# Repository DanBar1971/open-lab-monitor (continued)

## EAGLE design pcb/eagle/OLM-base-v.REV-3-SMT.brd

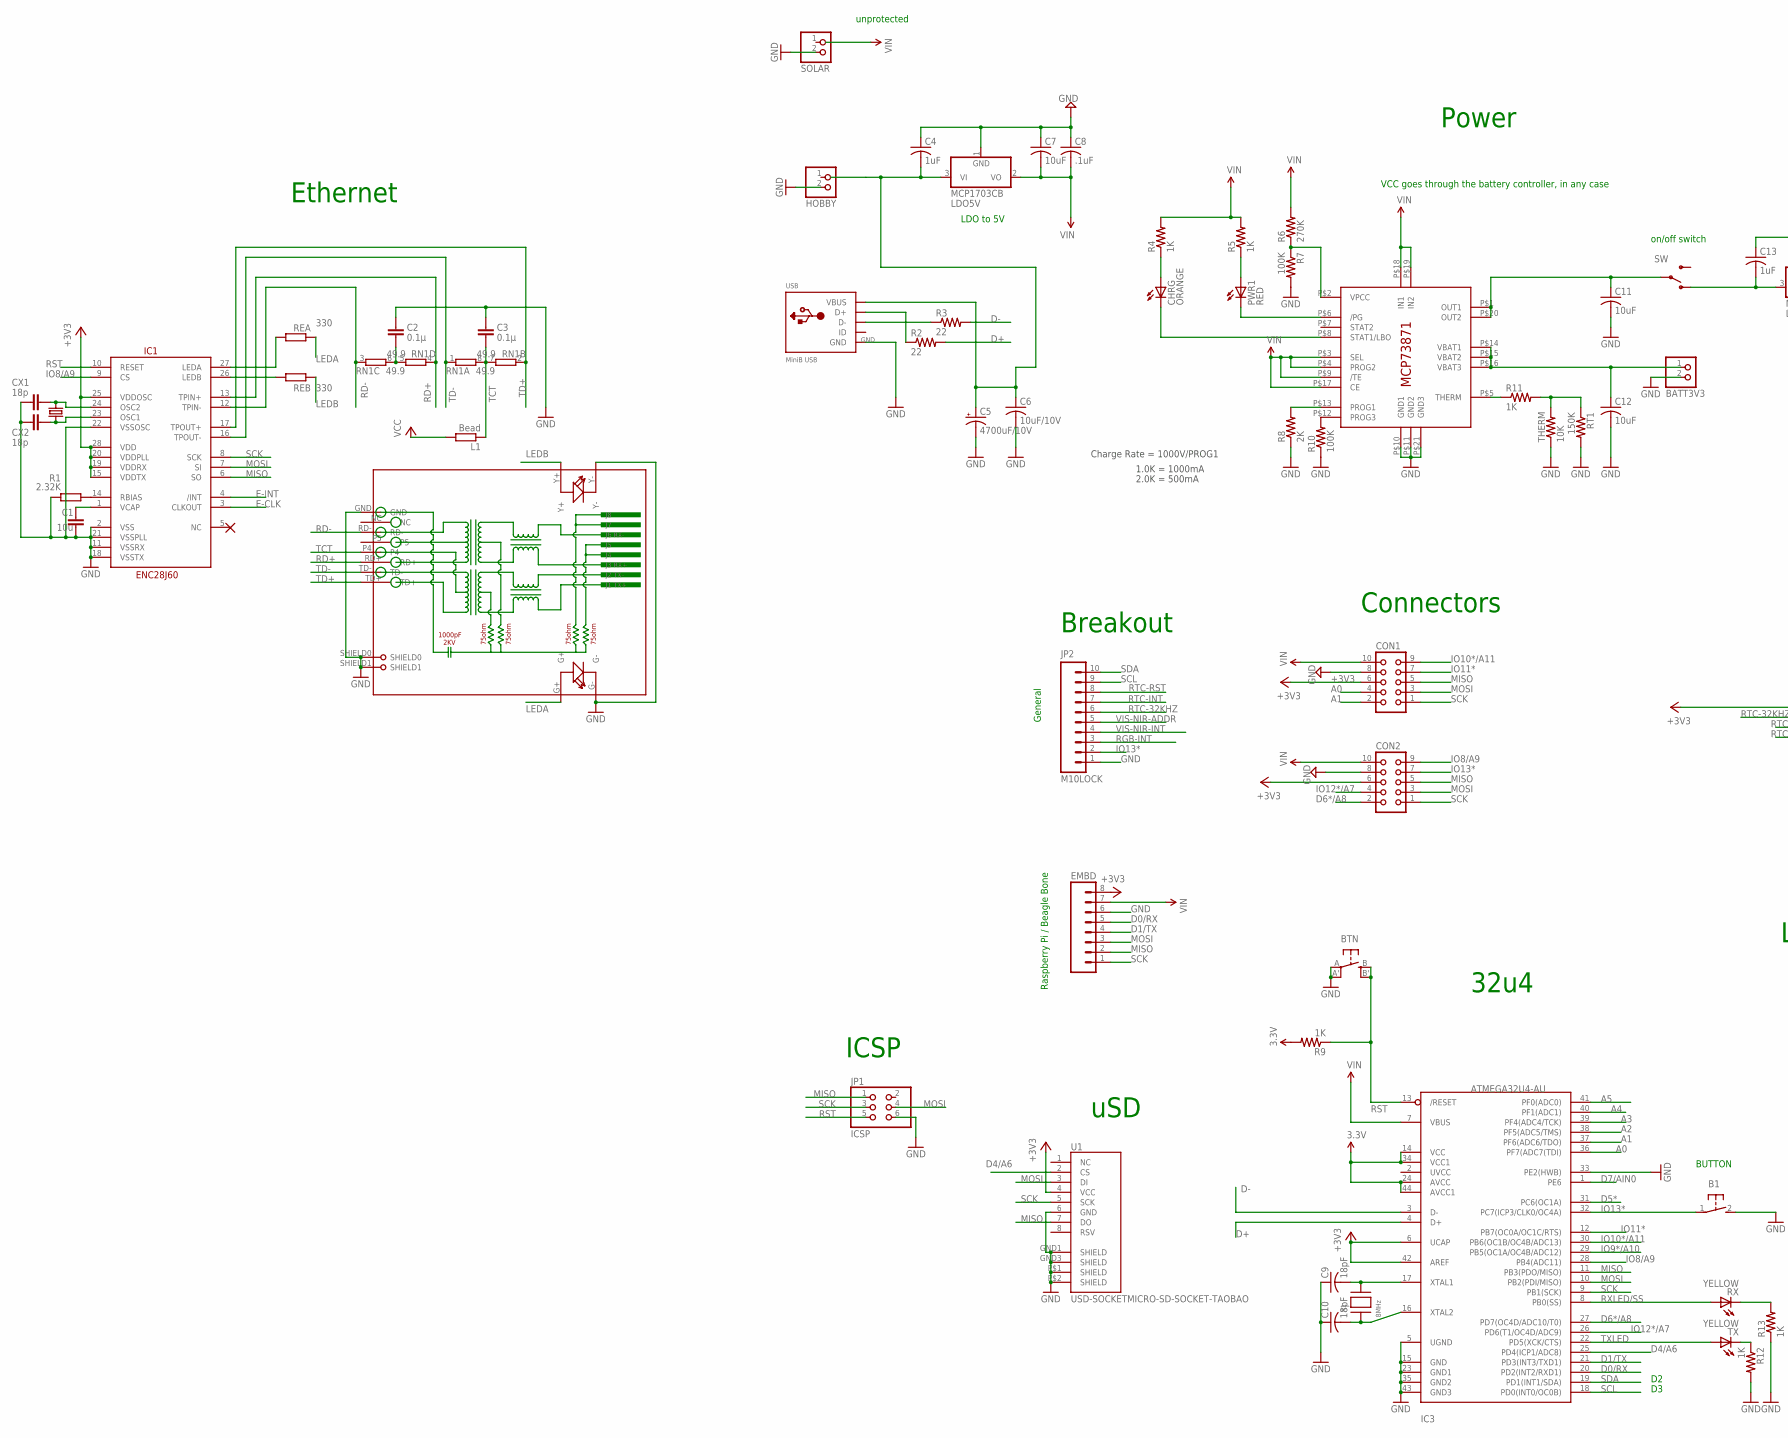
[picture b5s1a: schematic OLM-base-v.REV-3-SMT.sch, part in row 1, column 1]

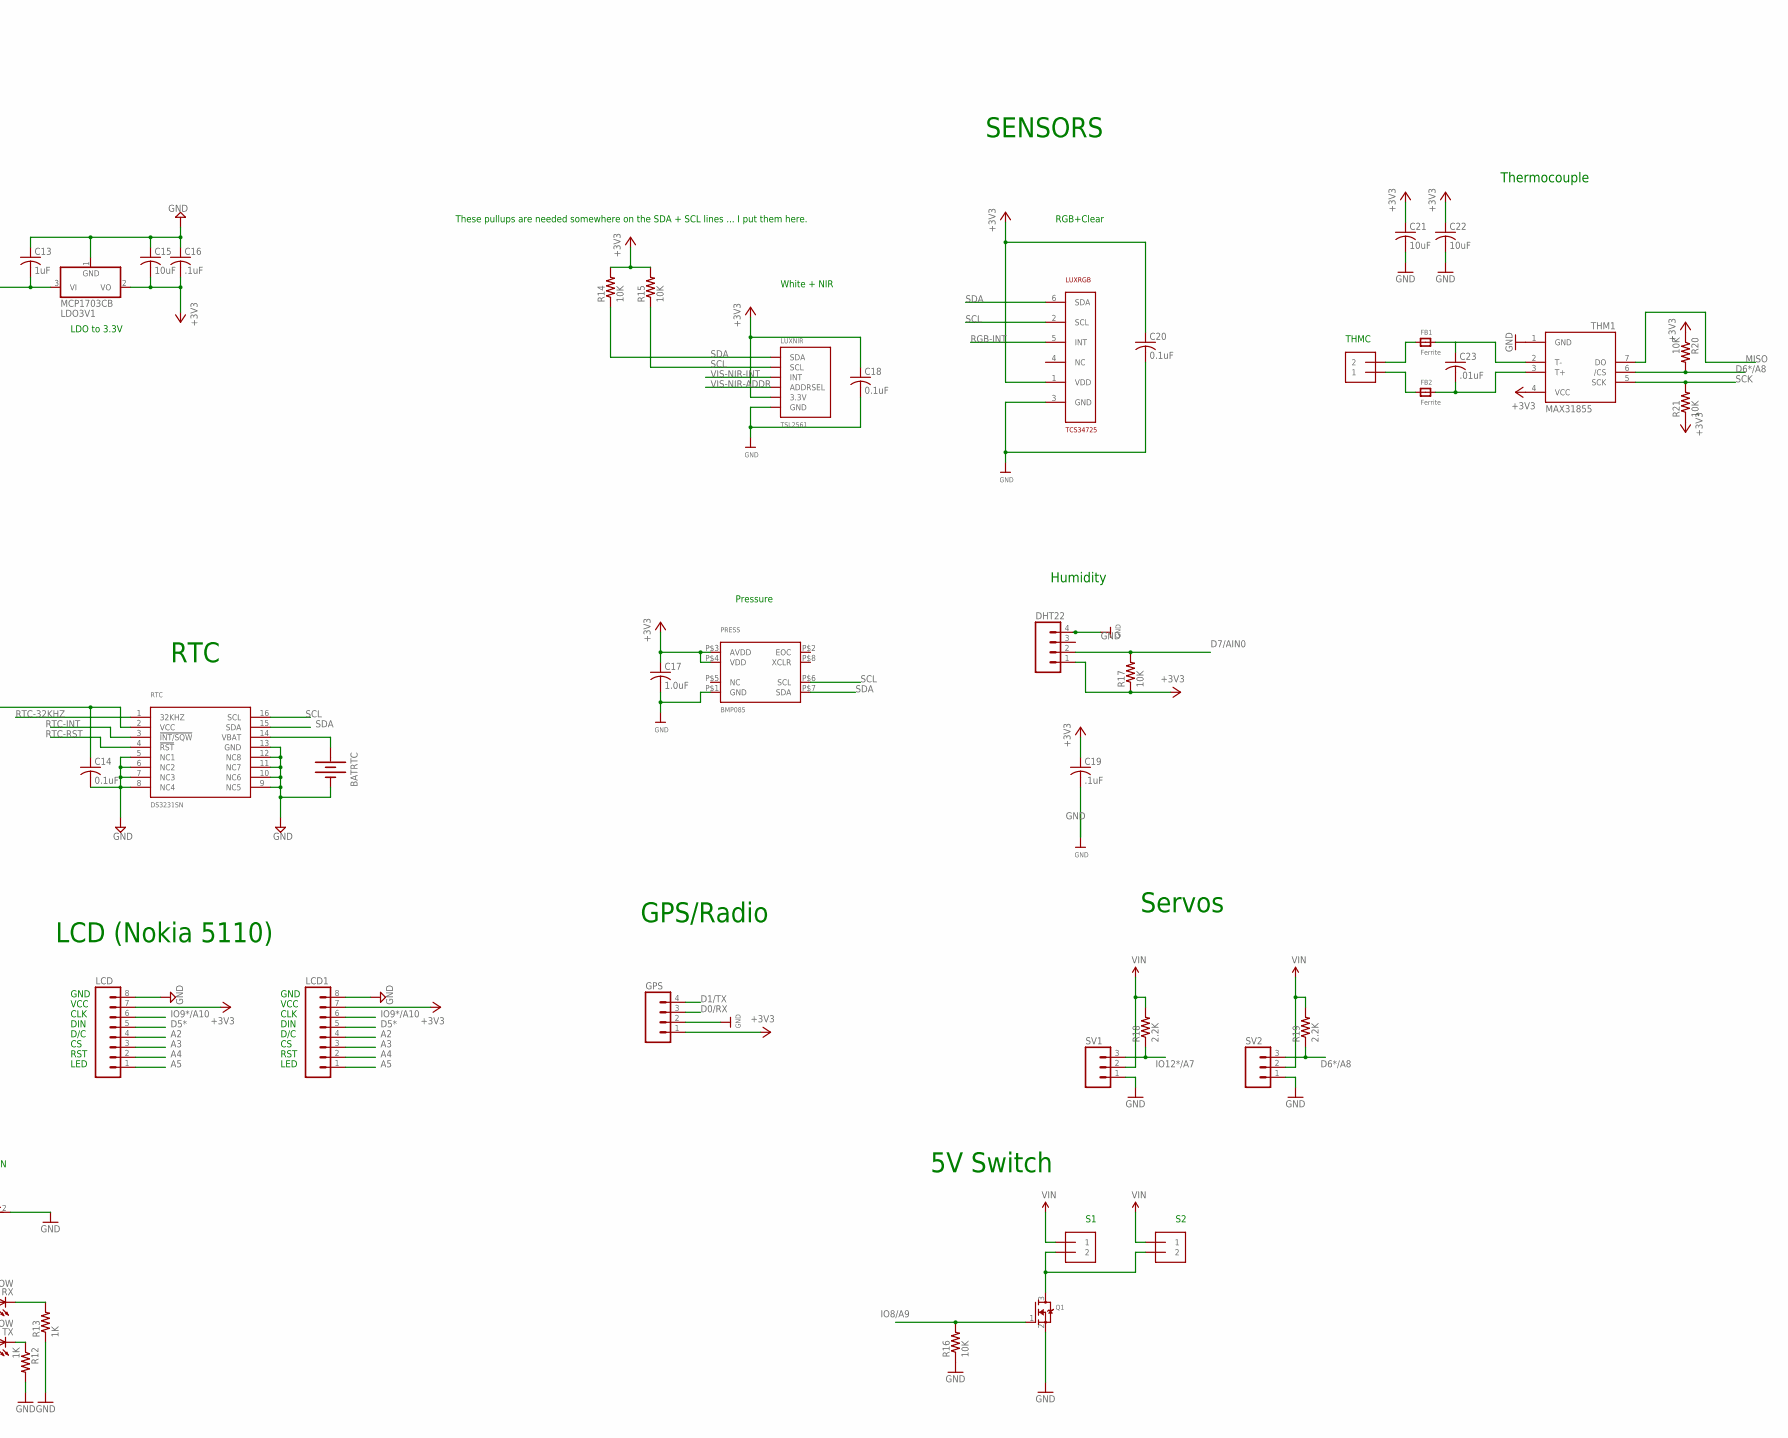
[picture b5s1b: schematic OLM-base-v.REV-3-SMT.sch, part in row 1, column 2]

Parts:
B1: 31-XX; B3F-31XX
BATRTC: BATTERYBATTERY_12MM_SMT; BATTCON_12MM_SMT
BATT3V3: JST_2PIN-SMT-RA; JST-PH-2-SMT-RA
BTN: EVQQ2; EVQ-Q2
C1: 10u; C0805
C2, C3: 0.1µ; C0805
C4, C13: 1uF; C0805
C5: 4700uF/10V; E5-13
C6: 10uF/10V; C0805
C7, C11, C12, C15, C21, C22: 10uF; C0805
C8, C16, C19: .1uF; C0805
C9, C10: 18pF; C0805
C14, C18, C20: 0.1uF; C0805
C17: 1.0uF; C0805
C23: .01uF; C0805
CHRG: ORANGE; CHIP-LED0805
CON1, CON2: CON10L
CX1, CX2: 18p; C0805
DHT22: M04LOCK; 1X04_LOCK
EMBD: M08LOCK; 1X08_LOCK
EXTL: 25MHz; CRYSTAL-SMD-10.5X4.8-2PIN
FB1, FB2: Ferrite; _0805
GPS: M04LOCK; 1X04_LOCK
HOBBY: JST_2PIN-SMT-RA; JST-PH-2-SMT-RA
IC1: ENC28J60; SOIC28WLONG
IC2: MCP73871; QFN20_4MM
IC3: ATMEGA32U4-AU; TQFP44
JP1: ICSP; 2X03
JP2: M10LOCK; 1X10_LOCK
L1: Bead; R0805
LCD, LCD1: M08LOCK; 1X08_LOCK
LDO3V1, LDO5V: MCP1703CB; SOT23
LUXNIR: TSL2561; TSL2561_FN@1
LUXRGB: TCS34725; DFN-6
PRESS: BMP085
PWR1: RED; CHIP-LED0805
Q1: MOSFET-NREFLOW; SOT23
R1: 2.32K; R0805
R2, R3: 22; R0805
R4, R5, R9, R12, R13: 1K; R0805
R6: 270K; R0805
R7, R10: 100K; R0805
R8: 2K; 0805-THM
R11: 1K; M0805
R14, R15, R16, R17, R20, R21: 10K; R0805
R18, R19: 2.2K; R0805
REA: 330; R0805
REB: 330; R0805
RJ1: HR911105A
RN1: 49.9; EXB38V
RT1: 150K; R0805
RTC: DS3231SN; SO16W
RX: YELLOW; CHIPLED_0805
S1, S2: 1X2-3.5MM
SOLAR: JST_2PIN-SMT-RA; JST-PH-2-SMT-RA
SV1, SV2: M03PTH; 1X03
SW: SPDT; SWITCH-SPDT-SMD
THERM: 10K; 0805-THM
THM1: MAX31855; SO08
THMC: 1X2-3.5MM
TX: YELLOW; CHIPLED_0805
U1: USD-SOCKETMICRO-SD-SOCKET-TAOBAO; MICRO-SD-SOCKET-TAOBAO
USB: MiniB USB; USB-MINIB_LARGER
X1: 8MHz; NX5032

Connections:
+3V3: C14.1, C15.2, C16.2, C17.1, C18.1, C19.1, C20.1, C21.1, C22.1, CON1.6, CON2.6, DHT22.1, EMBD.8, GPS.1, IC1.15 (VDDTX), IC1.19 (VDDRX), IC1.20 (VDDPLL), IC1.25 (VDDOSC), IC1.28 (VDD), IC3.6 (UCAP), IC3.42 (AREF), LCD.7, LCD1.7, LDO3V1.2 (VO), LUXNIR.VDD (3.3V), LUXRGB.1 (VDD), PRESS.P$3 (AVDD), PRESS.P$4 (VDD), R14.2, R15.2, R17.1, R20.1, R21.1, RTC.2 (VCC), THM1.4 (VCC), U1.4 (VCC)
A0: CON1.4, IC3.36 (PF7(ADC7(TDI))
A1: CON1.2, IC3.37 (PF6(ADC6/TDO))
A2: IC3.38 (PF5(ADC5/TMS)), LCD.4, LCD1.4
A3: IC3.39 (PF4(ADC4/TCK)), LCD.3, LCD1.3
A4: IC3.40 (PF1(ADC1)), LCD.2, LCD1.2
A5: IC3.41 (PF0(ADC0)), LCD.1, LCD1.1
BATT: BATT3V3.1 (2), C12.1, IC2.P$14 (VBAT1), IC2.P$15 (VBAT2), IC2.P$16 (VBAT3)
D0/RX: EMBD.5, GPS.3, IC3.20 (PD2(INT2/RXD1))
D1/TX: EMBD.4, GPS.4, IC3.21 (PD3(INT3/TXD1))
D4/A6: IC3.25 (PD4(ICP1/ADC8)), U1.2 (CS)
D5*: IC3.31 (PC6(OC1A)), LCD.5, LCD1.5
D6*/A8: CON2.2, IC3.27 (PD7(OC4D/ADC10/T0)), R19.1, R20.2, SV2.3, THM1.6 (/CS)
D7/AIN0: DHT22.2, IC3.1 (PE6), R17.2
D+: IC3.4 (D+), R2.2
D-: IC3.3 (D-), R3.2
E-CLK: IC1.3 (CLKOUT)
E-INT: IC1.4 (/INT)
GND: B1.2 (S), BATRTC.P$1 (-), BATT3V3.2 (1), BTN.A, BTN.A' (P1), C1.2, C2.1, C3.1, C4.1, C5.-, C6.2, C7.1, C8.1, C9.1, C10.1, C11.2, C12.2, C13.1, C14.2, C15.1, C16.1, C17.2, C18.2, C19.2, C20.2, C21.2, C22.2, CON1.8, CON2.8, CX1.2, CX2.2, DHT22.4, EMBD.6, GPS.2, HOBBY.2 (1), IC1.2 (VSS), IC1.11 (VSSRX), IC1.18 (VSSTX), IC1.21 (VSSPLL), IC1.22 (VSSOSC), IC2.P$10 (GND1), IC2.P$11 (GND2), IC2.P$21 (GND3), IC3.5 (UGND), IC3.15 (GND), IC3.23 (GND1), IC3.33 (PE2(HWB)), IC3.35 (GND2), IC3.43 (GND3), JP1.6, JP2.1, LCD.8, LCD1.8, LDO3V1.1 (GND), LDO5V.1 (GND), LUXNIR.VSS (GND), LUXRGB.3 (GND), PRESS.P$1 (GND), Q1.2 (S), R1.1, R7.2, R8.1, R10.1, R12.2, R13.1, R16.1, RJ1.G-, RJ1.GND, RJ1.SHIELD0, RJ1.SHIELD1, RJ1.Y-, RT1.2, RTC.5 (NC1), RTC.6 (NC2), RTC.7 (NC3), RTC.8 (NC4), RTC.9 (NC5), RTC.10 (NC6), RTC.11 (NC7), RTC.12 (NC8), RTC.13 (GND), SOLAR.2 (1), SV1.1, SV2.1, THERM.1, THM1.1 (GND), U1.6 (GND), U1.GND1 (SHIELD), U1.GND3 (SHIELD), U1.P$1 (SHIELD), U1.P$2 (SHIELD), USB.GND
HIGH-CURRENT: Q1.3 (D), S1.2, S2.2
IO8/A9: CON2.9, IC1.9 (CS), IC3.28 (PB4(ADC11)), Q1.1 (G), R16.2
IO9*/A10: IC3.29 (PB5(OC1A/OC4B/ADC12)), LCD.6, LCD1.6
IO10*/A11: CON1.9, IC3.30 (PB6(OC1B/OC4B/ADC13))
IO11*: CON1.7, IC3.12 (PB7(OC0A/OC1C/RTS))
IO12*/A7: CON2.4, IC3.26 (PD6(T1/OC4D/ADC9)), R18.1, SV1.3
IO13*: B1.1, CON2.7, IC3.32 (PC7(ICP3/CLK0/OC4A))
LEDA: REA.2, RJ1.G+
LEDB: REB.2, RJ1.Y+
MISO: CON1.5, CON2.5, EMBD.2, IC1.6 (SO), IC3.11 (PB3(PDO/MISO)), JP1.1, THM1.7 (DO), U1.7 (DO)
MOSI: CON1.3, CON2.3, EMBD.3, IC1.7 (SI), IC3.10 (PB2(PDI/MISO)), JP1.4, U1.3 (DI)
unnamed: BATRTC.P$2 (+), RTC.14 (VBAT)
unnamed: IC1.27 (LEDA), REA.1
unnamed: FB1.1, THMC.2
unnamed: C23.1, FB1.2, THM1.2 (T-)
unnamed: FB2.1, THMC.1
unnamed: C23.2, FB2.2, THM1.3 (T+)
unnamed: C9.2, IC3.17 (XTAL1), X1.P$2
unnamed: C10.2, IC3.16 (XTAL2), X1.P$1
unnamed: C2.2, RN1.5 (2), RN1.6 (2)
unnamed: R12.1, TX.C
unnamed: R13.2, RX.C
unnamed: IC1.26 (LEDB), REB.1
unnamed: C1.1, IC1.1 (VCAP)
unnamed: IC1.14 (RBIAS), R1.2
unnamed: CX1.1, EXTL.P$2 (2), IC1.24 (OSC2)
unnamed: CX2.1, EXTL.P$1 (1), IC1.23 (OSC1)
unnamed: IC2.P$2 (VPCC), R6.1, R7.1
unnamed: IC2.P$6 (/PG), PWR1.C
unnamed: C4.2, C5.+, C6.1, LDO5V.3 (VI), USB.VBUS
unnamed: CHRG.C, IC2.P$8 (STAT1/LBO)
unnamed: CHRG.A, R4.1
unnamed: PWR1.A, R5.1
unnamed: IC2.P$12 (PROG3), R10.2
unnamed: IC2.P$13 (PROG1), R8.2
unnamed: C11.1, IC2.P$1 (OUT1), IC2.P$20 (OUT2), SW.2
unnamed: IC2.P$5 (THERM), R11.1
unnamed: R11.2, RT1.1, THERM.2
unnamed: R2.1, USB.D+
unnamed: R3.1, USB.D-
unnamed: C13.2, LDO3V1.3 (VI)
RD+: IC1.13 (TPIN+), RJ1.RD+, RN1.4 (1)
RD-: IC1.12 (TPIN-), RJ1.RD-, RN1.3 (1)
RGB-INT: LUXRGB.5 (INT)
RST: BTN.B (S), BTN.B' (S1), IC1.10 (RESET), IC3.13 (/RESET), JP1.5, R9.1
RTC-32KHZ: RTC.1 (32KHZ)
RTC-INT: RTC.3 (!INT/SQW)
RTC-RST: RTC.4 (!RST)
RXLED/SS: IC3.8 (PB0(SS)), RX.A
SCK: CON1.1, CON2.1, EMBD.1, IC1.8 (SCK), IC3.9 (PB1(SCK)), JP1.3, R21.2, THM1.5 (SCK), U1.5 (SCK)
SCL: IC3.18 (PD0(INT0/OC0B)), JP2.9, LUXNIR.CLK (SCL), LUXRGB.2 (SCL), PRESS.P$6 (SCL), R15.1, RTC.16 (SCL)
SDA: IC3.19 (PD1(INT1/SDA)), JP2.10, LUXNIR.DATA (SDA), LUXRGB.6 (SDA), PRESS.P$7 (SDA), R14.1, RTC.15 (SDA)
TCT: C3.2, L1.1, RJ1.P4, RN1.7 (2), RN1.8 (2)
TD+: IC1.17 (TPOUT+), RJ1.TD+, RN1.2 (1)
TD-: IC1.16 (TPOUT-), RJ1.TD-, RN1.1
TXLED: IC3.22 (PD5(XCK/CTS)), TX.A
VCC: IC3.14 (VCC), IC3.24 (AVCC), IC3.34 (VCC1), IC3.44 (AVCC1), L1.2, R9.2
VIN: C7.2, C8.2, CON1.10, CON2.10, EMBD.7, IC2.P$3 (SEL), IC2.P$4 (PROG2), IC2.P$9 (/TE), IC2.P$17 (CE), IC2.P$18 (IN1), IC2.P$19 (IN2), IC3.7 (VBUS), LDO5V.2 (VO), R4.2, R5.2, R6.2, R18.2, R19.2, S1.1, S2.1, SV1.2, SV2.2
VIS-NIR-ADDR: LUXNIR.ADR (ADDRSEL)
VIS-NIR-INT: LUXNIR.INT

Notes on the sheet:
Power
uSD
32u4
Connectors
ICSP
Ethernet
Breakout
RTC
RGB+Clear
White + NIR
Pressure
Charge Rate = 1000V/PROG1
1.0K = 1000mA
2.0K = 500mA
Humidity
on/off switch
VCC goes through the battery controller, in any case
SENSORS
These pullups are needed somewhere on the SDA + SCL lines ... I put them here.
LED
RST
D/C
DIN
CLK
VCC
GND
Thermocouple
LDO to 5V
LDO to 3.3V
General
Raspberry Pi / Beagle Bone
unprotected
BUTTON
LCD (Nokia 5110)
GPS/Radio
Servos
5V Switch
THMC

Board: 2 copper layers, 95 parts (0 on the bottom side), 71 nets, no tracks yet.

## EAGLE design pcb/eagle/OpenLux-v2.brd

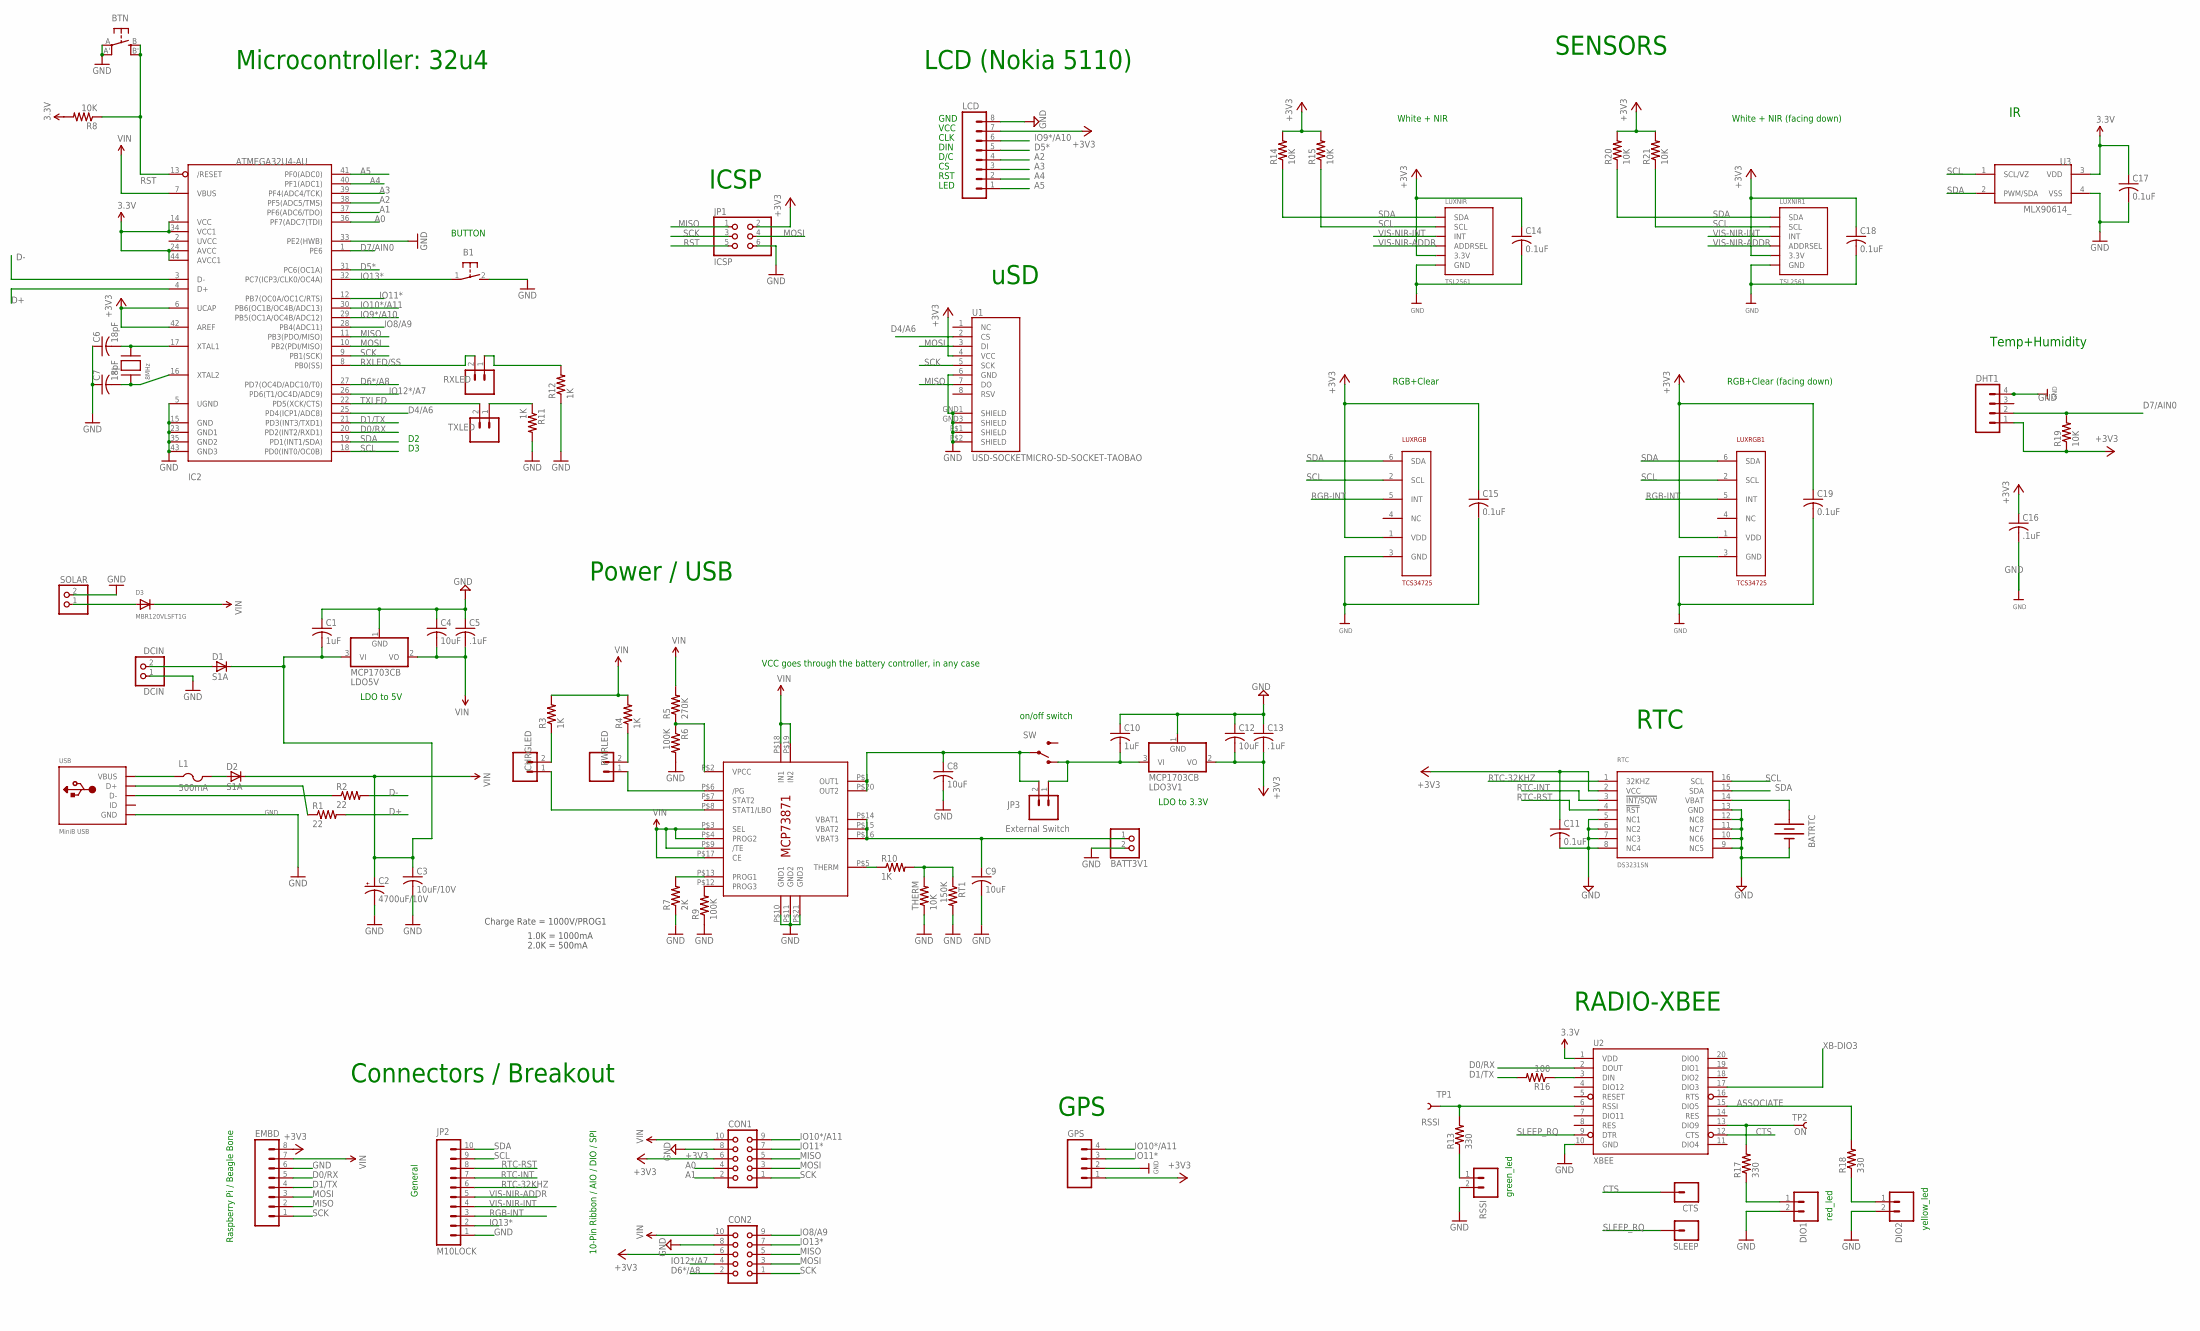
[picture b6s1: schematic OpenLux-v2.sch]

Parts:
B1: 31-XX; B3F-31XX
BATRTC: BATTERYBATTERY_12MM_SMT; BATTCON_12MM_SMT
BATT3V1: JST_2PIN-SMT-RA; JST-PH-2-SMT-RA
BTN: EVQQ2; EVQ-Q2
C1, C10: 1uF; C0805
C2: 4700uF/10V; E5-13
C3: 10uF/10V; C0805
C4, C8, C9, C12: 10uF; C0805
C5, C13, C16: .1uF; C0805
C6, C7: 18pF; C0805
C11, C14, C15, C17, C18, C19: 0.1uF; C0805
CHRGLED: M02PTH; 1X02
CON1, CON2: CON10L
CTS: M01PTH; 1X01
D1, D2: S1A; DO-214AC
D3: MBR120VLSFT1G; SOD-123
DCIN: DCIN; 1X02_OVAL
DHT1: M04LOCK; 1X04_LOCK
DIO1, DIO2: M02PTH; 1X02
EMBD: M08LOCK; 1X08_LOCK
GPS: M04LOCK; 1X04_LOCK
IC1: MCP73871; QFN20_4MM
IC2: ATMEGA32U4-AU; TQFP44
JP1: ICSP; 2X03
JP2: M10LOCK; 1X10_LOCK
JP3: External Switch; 1X02
L1: 500mA; R1206
LCD: M08LOCK; 1X08_LOCK
LDO3V1, LDO5V: MCP1703CB; SOT23
LUXNIR, LUXNIR1: TSL2561; TSL2561_FN@1
LUXRGB, LUXRGB1: TCS34725; DFN-6
PWRLED: M02PTH; 1X02
R1, R2: 22; R0805
R3, R4, R11, R12: 1K; R0805
R5: 270K; R0805
R6, R9: 100K; R0805
R7: 2K; 0805-THM
R8, R14, R15, R19, R20, R21: 10K; R0805
R10: 1K; M0805
R13, R17, R18: 330; R0805
R16: 100; R0805
RSSI: M02PTH; 1X02
RT1: 150K; R0805
RTC: DS3231SN; SO16W
RXLED: M02PTH; 1X02
SLEEP: M01PTH; 1X01
SOLAR: JST_2PIN-SMT-RA; JST-PH-2-SMT-RA
SW: SPDT; SWITCH-SPDT-SMD
THERM: 10K; 0805-THM
TP1: RSSI; PAD.03X.05
TP2: ON; PAD.03X.05
TXLED: M02PTH; 1X02
U1: USD-SOCKETMICRO-SD-SOCKET-TAOBAO; MICRO-SD-SOCKET-TAOBAO
U2: XBEE; XBEE-SMD
U3: MLX90614_; TO-39
USB: MiniB USB; USB-MINIB_LARGER
X1: 8MHz; NX5032

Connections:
3.3V: C17.1, U2.1 (VDD), U3.3 (VDD)
+3V3: C11.1, C12.2, C13.2, C14.1, C15.1, C16.1, C18.1, C19.1, CON1.6, CON2.6, DHT1.1, EMBD.8, GPS.1, IC2.6 (UCAP), IC2.42 (AREF), JP1.2, LCD.7, LDO3V1.2 (VO), LUXNIR.VDD (3.3V), LUXNIR1.VDD (3.3V), LUXRGB.1 (VDD), LUXRGB1.1 (VDD), R14.2, R15.2, R19.1, R20.2, R21.2, RTC.2 (VCC), U1.4 (VCC)
A0: CON1.4, IC2.36 (PF7(ADC7(TDI))
A1: CON1.2, IC2.37 (PF6(ADC6/TDO))
A2: IC2.38 (PF5(ADC5/TMS)), LCD.4
A3: IC2.39 (PF4(ADC4/TCK)), LCD.3
A4: IC2.40 (PF1(ADC1)), LCD.2
A5: IC2.41 (PF0(ADC0)), LCD.1
ASSOCIATE: R18.2, U2.15 (DIO5)
BATT: BATT3V1.1 (2), C9.1, IC1.P$14 (VBAT1), IC1.P$15 (VBAT2), IC1.P$16 (VBAT3)
CTS: CTS.1, U2.12 (CTS)
D0/RX: EMBD.5, IC2.20 (PD2(INT2/RXD1)), U2.2 (DOUT)
D1/TX: EMBD.4, IC2.21 (PD3(INT3/TXD1)), R16.2
D4/A6: IC2.25 (PD4(ICP1/ADC8)), U1.2 (CS)
D5*: IC2.31 (PC6(OC1A)), LCD.5
D6*/A8: CON2.2, IC2.27 (PD7(OC4D/ADC10/T0))
D7/AIN0: DHT1.2, IC2.1 (PE6), R19.2
D+: IC2.4 (D+), R1.2
D-: IC2.3 (D-), R2.2
GND: B1.2 (S), BATRTC.P$1 (-), BATT3V1.2 (1), BTN.A, BTN.A' (P1), C1.1, C2.-, C3.2, C4.1, C5.1, C6.1, C7.1, C8.2, C9.2, C10.1, C11.2, C12.1, C13.1, C14.2, C15.2, C16.2, C17.2, C18.2, C19.2, CON1.8, CON2.8, DCIN.1, DHT1.4, DIO1.2, DIO2.2, EMBD.6, GPS.2, IC1.P$10 (GND1), IC1.P$11 (GND2), IC1.P$21 (GND3), IC2.5 (UGND), IC2.15 (GND), IC2.23 (GND1), IC2.33 (PE2(HWB)), IC2.35 (GND2), IC2.43 (GND3), JP1.6, JP2.1, LCD.8, LDO3V1.1 (GND), LDO5V.1 (GND), LUXNIR.VSS (GND), LUXNIR1.VSS (GND), LUXRGB.3 (GND), LUXRGB1.3 (GND), R6.2, R7.1, R9.1, R11.2, R12.1, RSSI.2, RT1.2, RTC.5 (NC1), RTC.6 (NC2), RTC.7 (NC3), RTC.8 (NC4), RTC.9 (NC5), RTC.10 (NC6), RTC.11 (NC7), RTC.12 (NC8), RTC.13 (GND), SOLAR.2 (1), THERM.1, U1.6 (GND), U1.GND1 (SHIELD), U1.GND3 (SHIELD), U1.P$1 (SHIELD), U1.P$2 (SHIELD), U2.10 (GND), U3.4 (VSS), USB.GND
IO8/A9: CON2.9, IC2.28 (PB4(ADC11))
IO9*/A10: IC2.29 (PB5(OC1A/OC4B/ADC12)), LCD.6
IO10*/A11: CON1.9, GPS.4, IC2.30 (PB6(OC1B/OC4B/ADC13))
IO11*: CON1.7, GPS.3, IC2.12 (PB7(OC0A/OC1C/RTS))
IO12*/A7: CON2.4, IC2.26 (PD6(T1/OC4D/ADC9))
IO13*: B1.1, CON2.7, IC2.32 (PC7(ICP3/CLK0/OC4A)), JP2.2
MISO: CON1.5, CON2.5, EMBD.2, IC2.11 (PB3(PDO/MISO)), JP1.1, U1.7 (DO)
MOSI: CON1.3, CON2.3, EMBD.3, IC2.10 (PB2(PDI/MISO)), JP1.4, U1.3 (DI)
unnamed: BATRTC.P$2 (+), RTC.14 (VBAT)
unnamed: R17.2, TP2.P$1, U2.13 (DIO9)
unnamed: R13.1, RSSI.1
unnamed: R13.2, TP1.P$1, U2.6 (RSSI)
unnamed: R16.1, U2.3 (DIN)
unnamed: DIO1.1, R17.1
unnamed: D1.A, DCIN.2
unnamed: C6.2, IC2.17 (XTAL1), X1.P$2
unnamed: C7.2, IC2.16 (XTAL2), X1.P$1
unnamed: R11.1, TXLED.1
unnamed: R12.2, RXLED.1
unnamed: L1.1, USB.VBUS
unnamed: DIO2.1, R18.1
unnamed: IC1.P$2 (VPCC), R5.1, R6.1
unnamed: IC1.P$6 (/PG), PWRLED.1
unnamed: D3.A, SOLAR.1 (2)
unnamed: D2.A, L1.2
unnamed: CHRGLED.1, IC1.P$8 (STAT1/LBO)
unnamed: CHRGLED.2, R3.1
unnamed: PWRLED.2, R4.1
unnamed: IC1.P$12 (PROG3), R9.2
unnamed: IC1.P$13 (PROG1), R7.2
unnamed: C8.1, IC1.P$1 (OUT1), IC1.P$20 (OUT2), JP3.2, SW.2
unnamed: IC1.P$5 (THERM), R10.1
unnamed: R10.2, RT1.1, THERM.2
unnamed: R1.1, USB.D+
unnamed: R2.1, USB.D-
unnamed: C10.2, JP3.1, LDO3V1.3 (VI), SW.1 (O)
RGB-INT: JP2.3, LUXRGB.5 (INT), LUXRGB1.5 (INT)
RST: BTN.B (S), BTN.B' (S1), IC2.13 (/RESET), JP1.5, R8.1
RTC-32KHZ: JP2.6, RTC.1 (32KHZ)
RTC-INT: JP2.7, RTC.3 (!INT/SQW)
RTC-RST: JP2.8, RTC.4 (!RST)
RXLED/SS: IC2.8 (PB0(SS)), RXLED.2
SCK: CON1.1, CON2.1, EMBD.1, IC2.9 (PB1(SCK)), JP1.3, U1.5 (SCK)
SCL: IC2.18 (PD0(INT0/OC0B)), JP2.9, LUXNIR.CLK (SCL), LUXNIR1.CLK (SCL), LUXRGB.2 (SCL), LUXRGB1.2 (SCL), R15.1, R21.1, RTC.16 (SCL), U3.1 (SCL/VZ)
SDA: IC2.19 (PD1(INT1/SDA)), JP2.10, LUXNIR.DATA (SDA), LUXNIR1.DATA (SDA), LUXRGB.6 (SDA), LUXRGB1.6 (SDA), R14.1, R20.1, RTC.15 (SDA), U3.2 (PWM/SDA)
SLEEP_RQ: SLEEP.1, U2.9 (DTR)
TXLED: IC2.22 (PD5(XCK/CTS)), TXLED.2
VCC: IC2.14 (VCC), IC2.24 (AVCC), IC2.34 (VCC1), IC2.44 (AVCC1), R8.2
VIN: C1.2, C2.+, C3.1, C4.2, C5.2, CON1.10, CON2.10, D1.C, D2.C, D3.C, EMBD.7, IC1.P$3 (SEL), IC1.P$4 (PROG2), IC1.P$9 (/TE), IC1.P$17 (CE), IC1.P$18 (IN1), IC1.P$19 (IN2), IC2.7 (VBUS), LDO5V.2 (VO), LDO5V.3 (VI), R3.2, R4.2, R5.2
VIS-NIR-ADDR: JP2.5, LUXNIR.ADR (ADDRSEL), LUXNIR1.ADR (ADDRSEL)
VIS-NIR-INT: JP2.4, LUXNIR.INT, LUXNIR1.INT
XB-DIO3: U2.17 (DIO3)

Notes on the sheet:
Power / USB
uSD
Microcontroller: 32u4
Connectors / Breakout
ICSP
RTC
RGB+Clear
White + NIR
Charge Rate = 1000V/PROG1
1.0K = 1000mA
2.0K = 500mA
Temp+Humidity
on/off switch
VCC goes through the battery controller, in any case
SENSORS
LED
RST
D/C
DIN
CLK
VCC
GND
LDO to 5V
LDO to 3.3V
General
Raspberry Pi / Beagle Bone
BUTTON
LCD (Nokia 5110)
GPS
red_led
yellow_led
green_led
RADIO-XBEE
10-Pin Ribbon / AIO / DIO / SPI
RGB+Clear (facing down)
White + NIR (facing down)

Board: 2 copper layers, 87 parts (3 on the bottom side), 71 nets, no tracks yet.

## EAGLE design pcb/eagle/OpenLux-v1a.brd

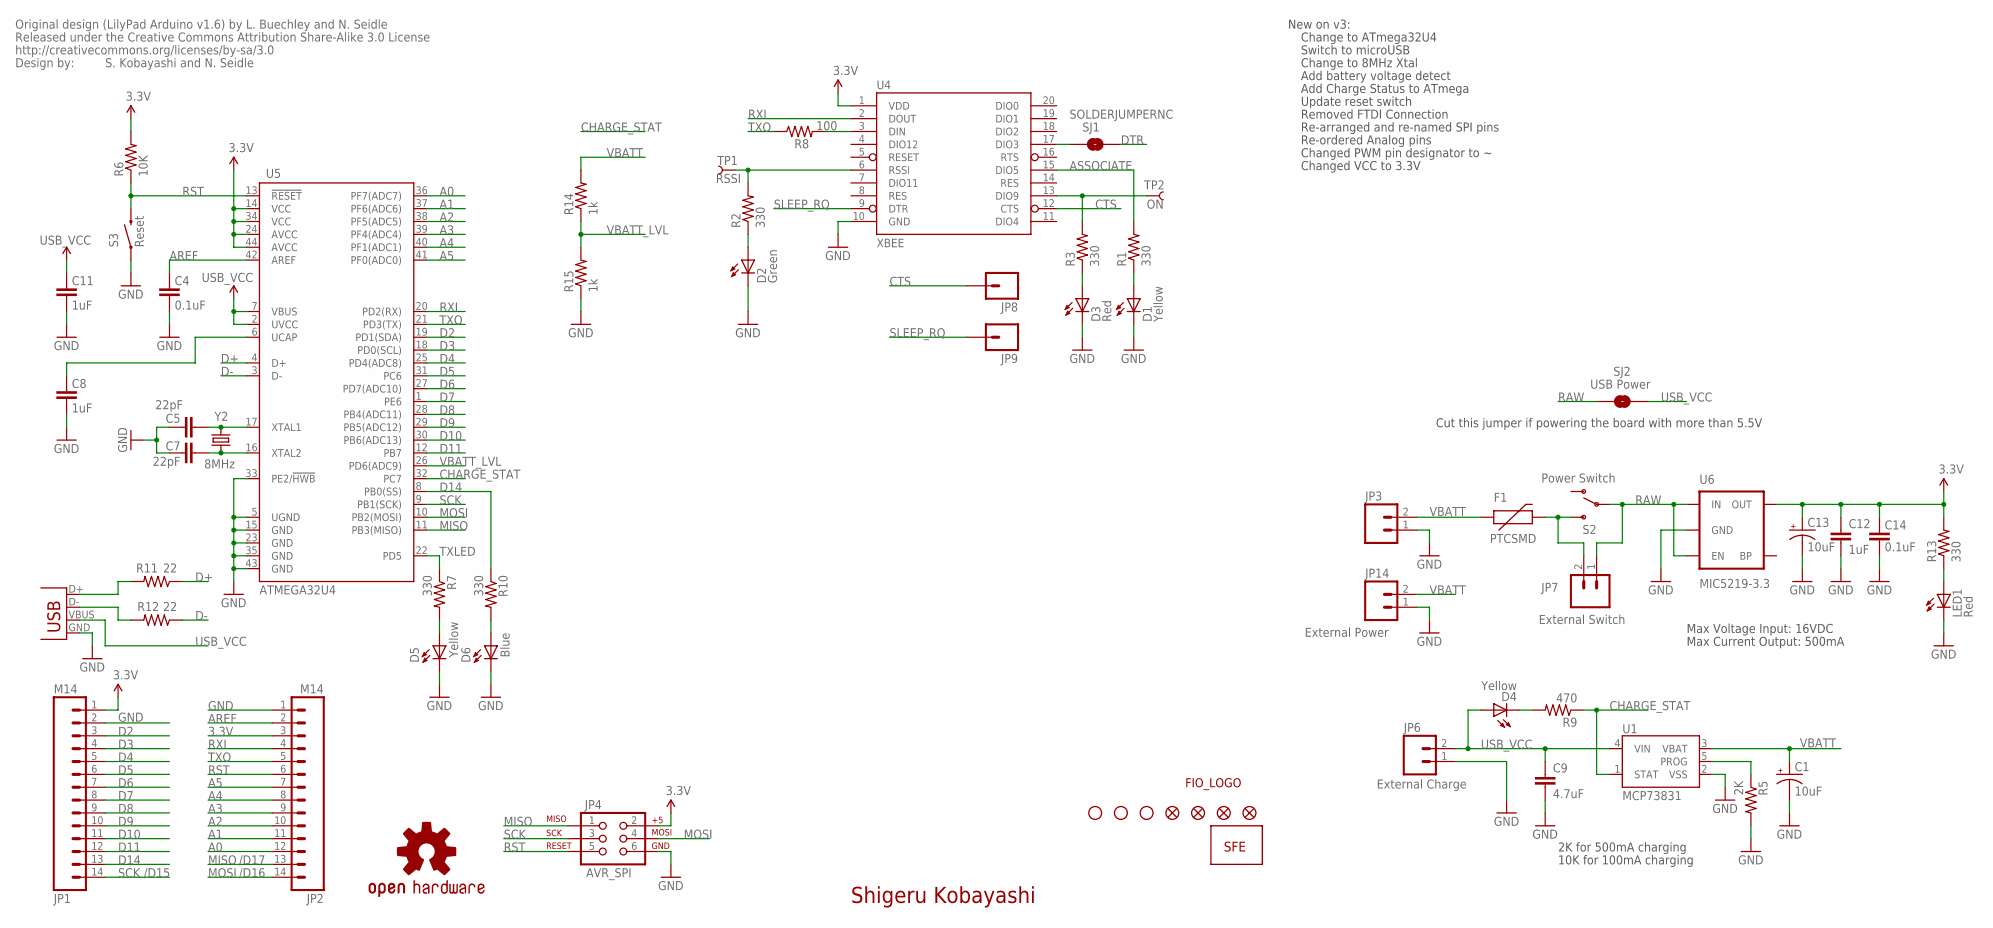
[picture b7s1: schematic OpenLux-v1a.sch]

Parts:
C1, C13: 10uF; EIA3216
C4, C14: 0.1uF; 0402-CAP
C5, C7: 22pF; 0402-CAP
C8, C11, C12: 1uF; 0402-CAP
C9: 4.7uF; 0402-CAP
D1, D4, D5: Yellow; LED-0603
D2: Green; LED-0603
D3: Red; LED-0603
D6: Blue; LED-0603
F1: PTCSMD; PTC-1206
JP1, JP2: M14; 1X14
JP3: M02-JST-2MM-SMT; JST-2-SMD
JP4: AVR_SPI; 2X3
JP5, JP16, JP17: STAND-OFF
JP6: External Charge; 1X02
JP7: External Switch; 1X02
JP8, JP9: M01PTH; 1X01
JP10, JP11, JP12, JP13: FIDUCIALUFIDUCIAL; FIDUCIAL-1X2
JP14: External Power; 1X02
LED1: Red; LED-0603
R1, R2, R3, R7, R10, R13: 330; 0402-RES
R5: 2K; 0402-RES
R6: 10K; 0402-RES
R8: 100; 0402-RES
R9: 470; 0402-RES
R11, R12: 22; 0402-RES
R14, R15: 1k; 0402-RES
S2: Power Switch; AYZ0202
S3: Reset; TACTILE_SWITCH_SMD
SJ1: SOLDERJUMPERNC; SJ_2S
SJ2: USB Power; SJ_2S-TRACE
TP1: RSSI; PAD.03X.05
TP2: ON; PAD.03X.05
U1: MCP73831; SOT23-5
U4: XBEE; XBEE-SMD
U5: ATMEGA32U4; QFN-44-NOPAD
U6: MIC5219-3.3; SOT23-5
U$1: LOGO-SFENEW; SFE-NEW-WEBLOGO
U$2: OSHW-LOGOS; OSHW-LOGO-S
U$3: CREATIVE_COMMONS
U$6: FIO_LOGOV2; FUNNEL_LOGO_BOTTOM_V2
X2: USB-MICROB
Y2: 8MHz; CRYSTAL-SMD-5X3

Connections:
3.3V: C12.1, C13.A (+), C14.2, JP1.1, JP2.3, JP4.2, R6.2, R13.2, U4.1 (VDD), U5.14 (VCC), U5.24 (AVCC), U5.34 (VCC), U5.44 (AVCC), U6.5 (OUT)
A0: JP2.12, U5.36 (PF7(ADC7))
A1: JP2.11, U5.37 (PF6(ADC6))
A2: JP2.10, U5.38 (PF5(ADC5))
A3: JP2.9, U5.39 (PF4(ADC4))
A4: JP2.8, U5.40 (PF1(ADC1))
A5: JP2.7, U5.41 (PF0(ADC0))
AREF: C4.2, JP2.2, U5.42 (AREF)
ASSOCIATE: R1.2, U4.15 (DIO5)
CHARGE_STAT: R9.1, U1.1 (STAT), U5.32 (PC7)
CTS: JP8.1, U4.12 (CTS)
D2: JP1.3, U5.19 (PD1(SDA))
D3: JP1.4, U5.18 (PD0(SCL))
D4: JP1.5, U5.25 (PD4(ADC8))
D5: JP1.6, U5.31 (PC6)
D6: JP1.7, U5.27 (PD7(ADC10))
D7: JP1.8, U5.1 (PE6)
D8: JP1.9, U5.28 (PB4(ADC11))
D9: JP1.10, U5.29 (PB5(ADC12))
D10: JP1.11, U5.30 (PB6(ADC13))
D11: JP1.12, U5.12 (PB7)
D14: JP1.13, R10.1, U5.8 (PB0(SS))
D+: R11.1, U5.4 (D+)
D-: R12.1, U5.3 (D-)
DTR: SJ1.2
GND: C1.C (-), C4.1, C5.2, C7.2, C8.1, C9.2, C11.1, C12.2, C13.C (-), C14.1, D1.C, D2.C, D3.C, D5.C, D6.C, JP1.2, JP2.1, JP3.1, JP4.6, JP6.1, JP14.1, LED1.C, R5.2, R15.1, S3.1, U1.2 (VSS), U4.10 (GND), U5.5 (UGND), U5.15 (GND), U5.23 (GND), U5.33 (PE2/!HWB), U5.35 (GND), U5.43 (GND), U6.2 (GND), X2.GND
MISO: JP2.13, JP4.1, U5.11 (PB3(MISO))
MOSI: JP2.14, JP4.4, U5.10 (PB2(MOSI))
unnamed: R3.2, TP2.P$1, U4.13 (DIO9)
unnamed: D1.A, R1.1
unnamed: D2.A, R2.1
unnamed: R2.2, TP1.P$1, U4.6 (RSSI)
unnamed: D3.A, R3.1
unnamed: R8.2, U4.3 (DIN)
unnamed: D4.C, R9.2
unnamed: F1.2, JP7.2, S2.3 (S)
unnamed: R5.1, U1.5 (PROG)
unnamed: SJ1.1, U4.17 (DIO3)
unnamed: D5.A, R7.2
unnamed: C7.1, U5.16 (XTAL2), Y2.1
unnamed: C5.1, U5.17 (XTAL1), Y2.3 (2)
unnamed: D6.A, R10.2
unnamed: R12.2, X2.D-
unnamed: R11.2, X2.D+
unnamed: LED1.A, R13.1
RAW: JP7.1, S2.2, SJ2.1, U6.1 (IN), U6.3 (EN)
RST: JP2.6, JP4.5, R6.1, S3.3 (2), U5.13 (!RESET)
RXI: JP2.4, U4.2 (DOUT), U5.20 (PD2(RX))
SCK: JP1.14, JP4.3, U5.9 (PB1(SCK))
SLEEP_RQ: JP9.1, U4.9 (DTR)
TXLED: R7.1, U5.22 (PD5)
TXO: JP2.5, R8.1, U5.21 (PD3(TX))
UCAP: C8.2, U5.6 (UCAP)
USB_VCC: C9.1, C11.2, D4.A, JP6.2, SJ2.2, U1.4 (VIN), U5.2 (UVCC), U5.7 (VBUS), X2.VBUS
VBATT: C1.A (+), F1.1, JP3.2, JP14.2, R14.2, U1.3 (VBAT)
VBATT_LVL: R14.1, R15.2, U5.26 (PD6(ADC9))

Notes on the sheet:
Shigeru Kobayashi
/D16
/D17
/D15
Original design (LilyPad Arduino v1.6) by L. Buechley and N. Seidle
S. Kobayashi and N. Seidle
Change to ATmega32U4
Switch to microUSB
New on v3:
Change to 8MHz Xtal
Max Voltage Input: 16VDC
Max Current Output: 500mA
Cut this jumper if powering the board with more than 5.5V
2K for 500mA charging
10K for 100mA charging
Add battery voltage detect
Add Charge Status to ATmega
Update reset switch
Removed FTDI Connection
Re-arranged and re-named SPI pins
Re-ordered Analog pins
Changed PWM pin designator to ~
Changed VCC to 3.3V

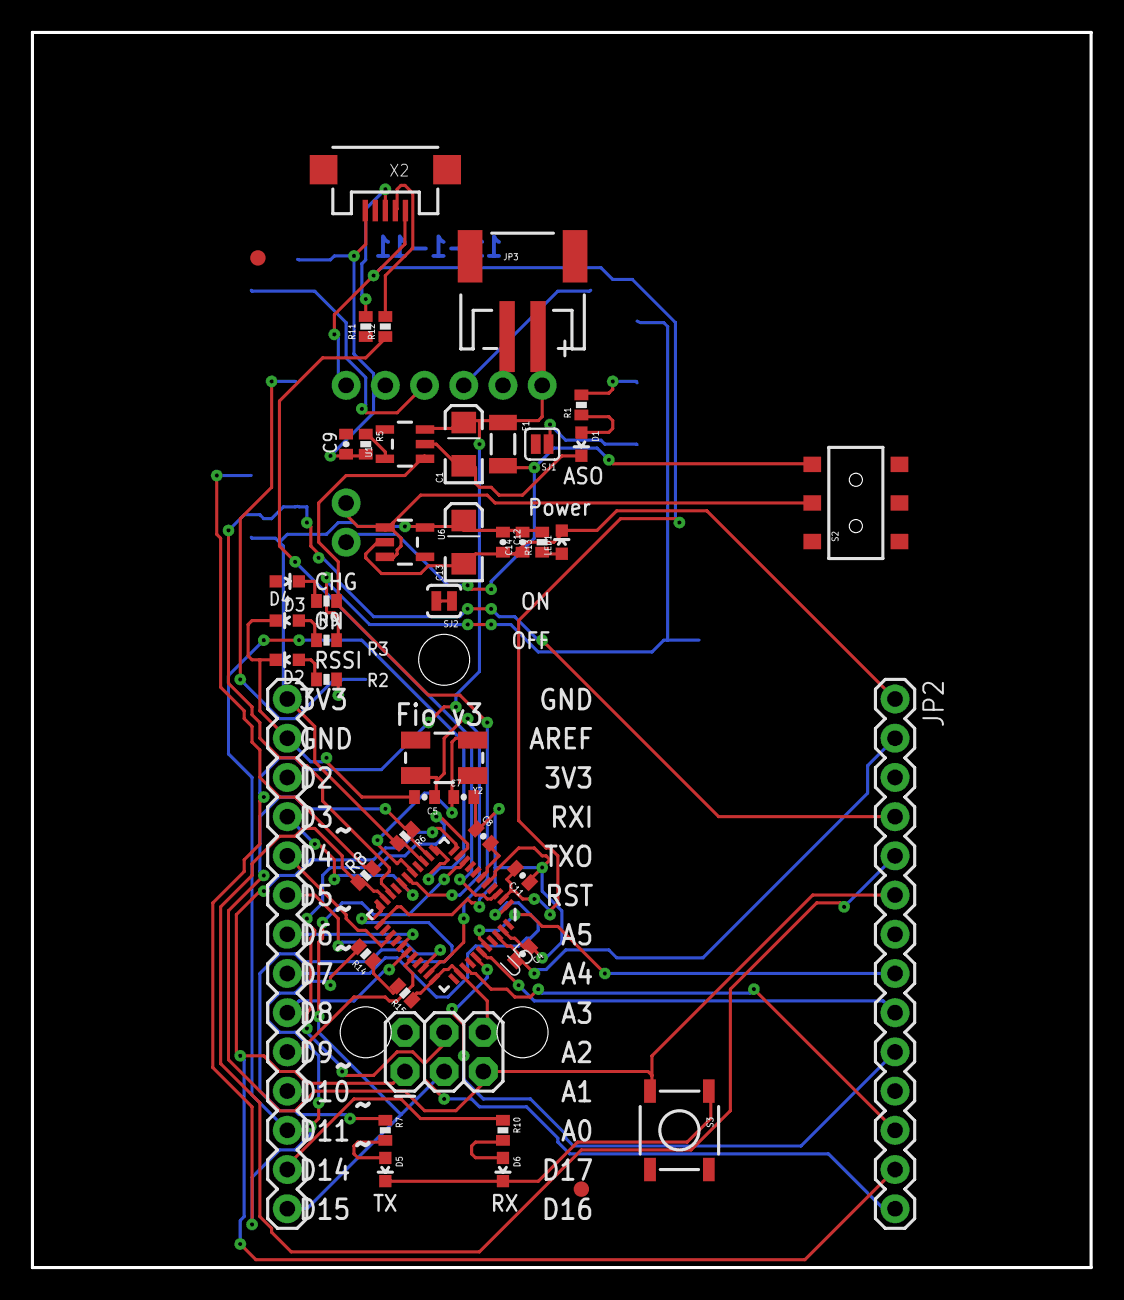
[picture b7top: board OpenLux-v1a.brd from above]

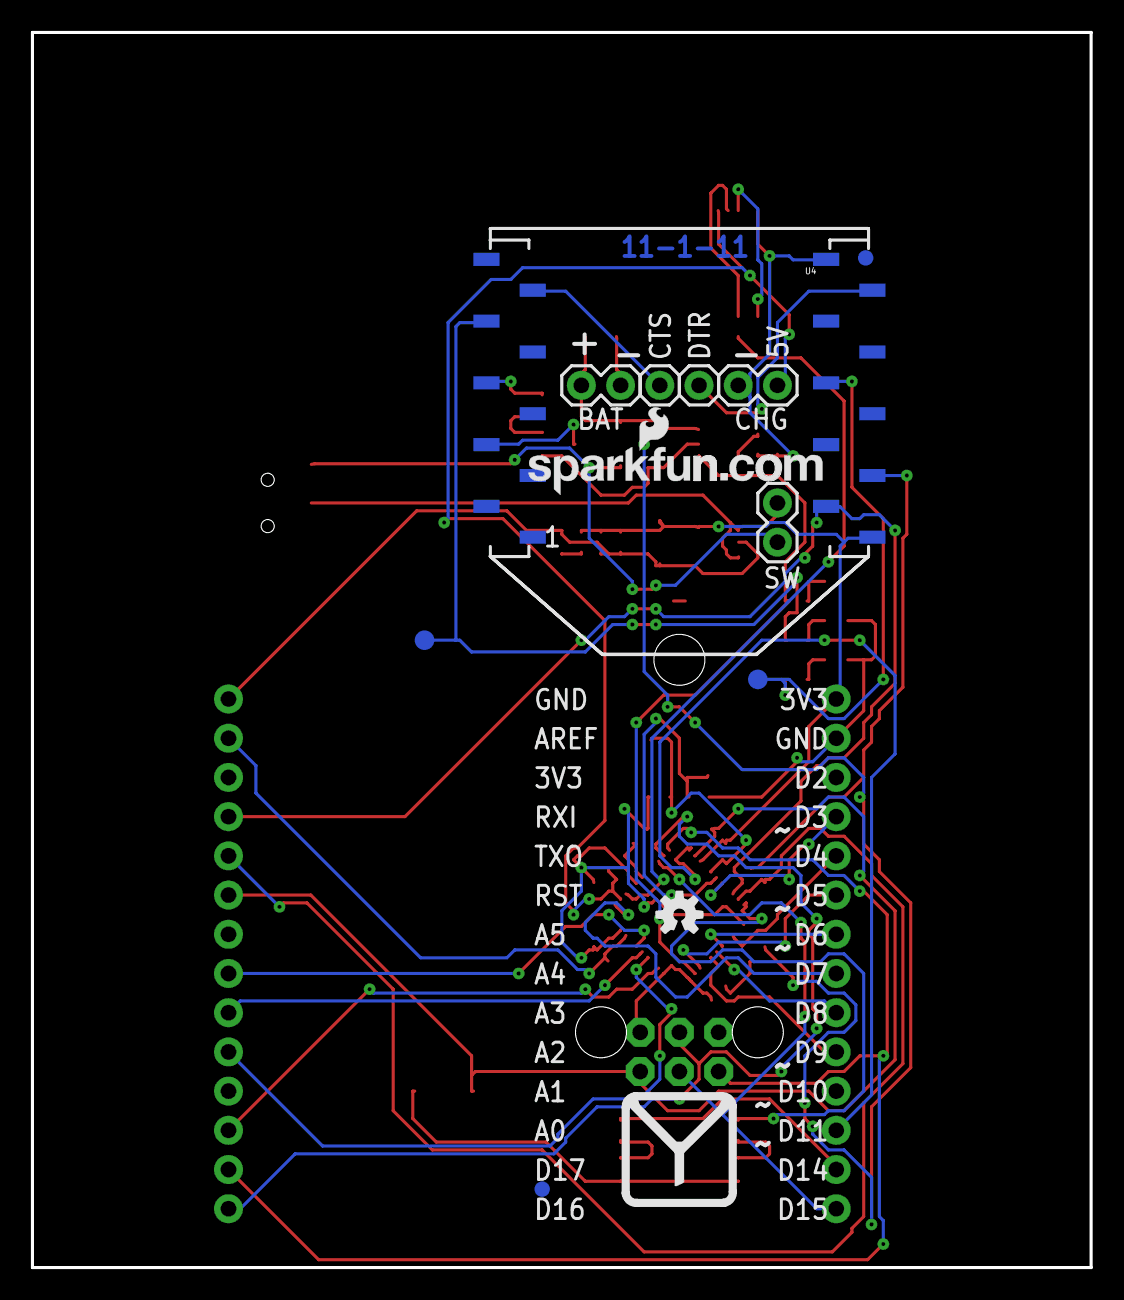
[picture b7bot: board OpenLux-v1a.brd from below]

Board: 2 copper layers, 68.6 x 80.0 mm, 64 parts (12 on the bottom side), 55 nets.
